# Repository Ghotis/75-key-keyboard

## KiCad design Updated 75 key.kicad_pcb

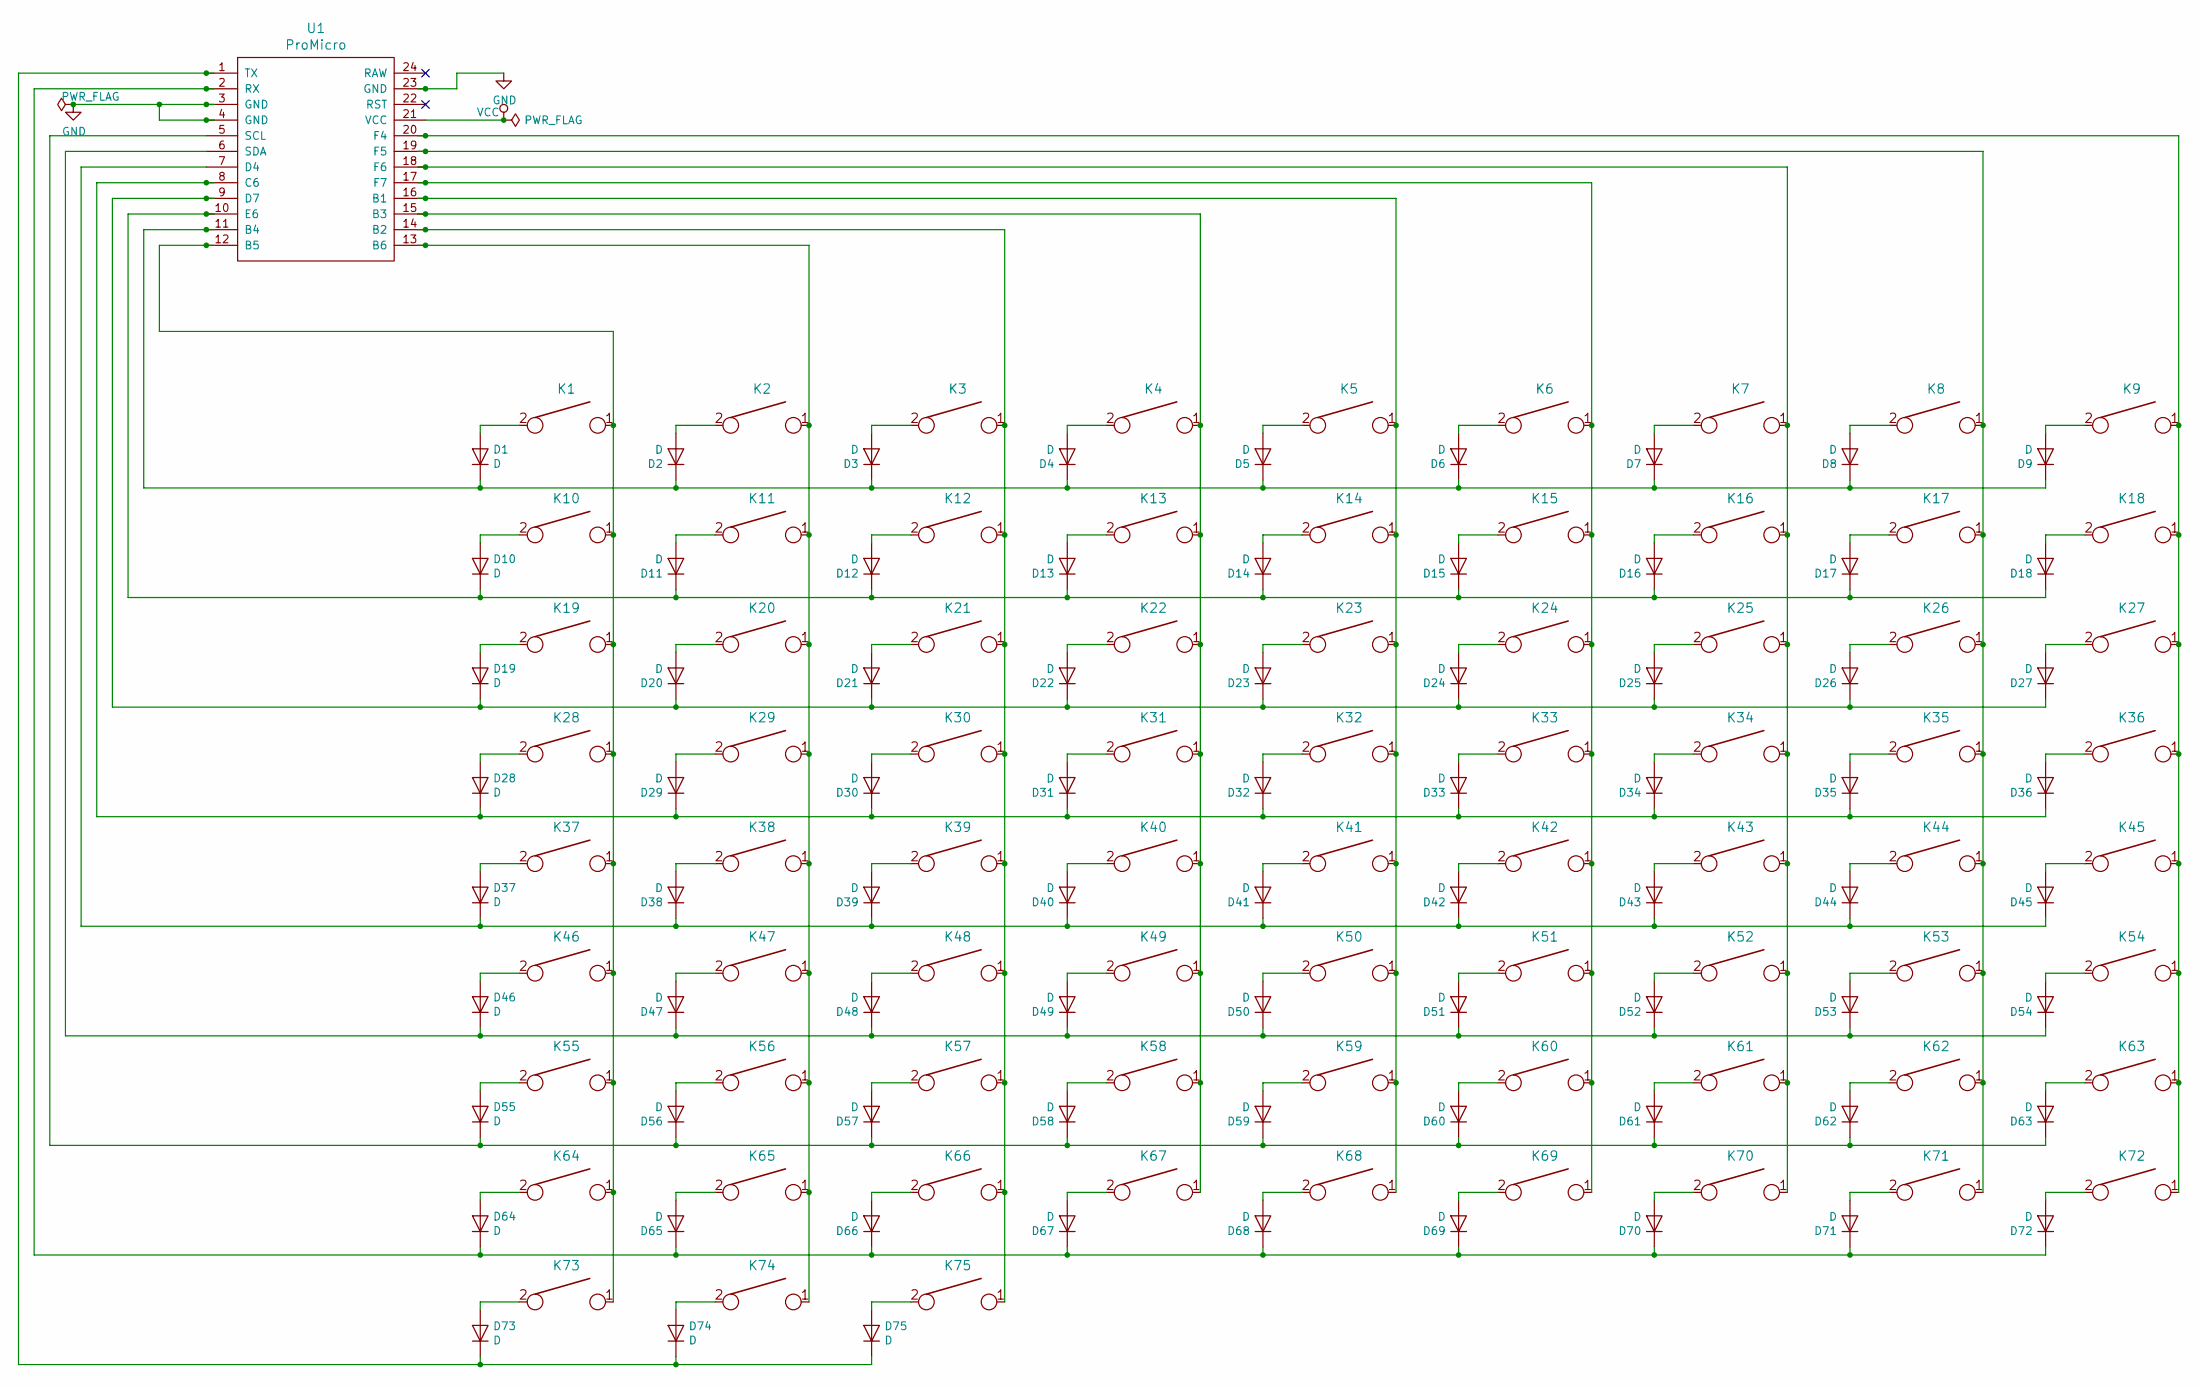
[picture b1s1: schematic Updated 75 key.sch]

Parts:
D1, D2, D3, D4, D5, D6, D7, D8, D9, D10, D11, D12, D13, D14, D15, D16, D17, D18, D19, D20, D21, D22, D23, D24, D25, D26, D27, D28, D29, D30, D31, D32, D33, D34, D35, D36, D37, D38, D39, D40, D41, D42, D43, D44, D45, D46, D47, D48, D49, D50, D51, D52, D53, D54, D55, D56, D57, D58, D59, D60, D61, D62, D63, D64, D65, D66, D67, D68, D69, D70, D71, D72, D73, D74, D75: D; D_SOD123_axial
K1, K2, K3, K4, K5, K6, K7, K8, K9, K10, K11, K12, K13, K14, K15, K16, K17, K18, K19, K20, K21, K22, K23, K24, K25, K26, K27, K28, K29, K30, K31, K32, K33, K34, K35, K36, K37, K38, K39, K40, K41, K42, K43, K44, K45, K46, K47, K48, K49, K50, K51, K52, K53, K54, K55, K56, K57, K58, K59, K60, K61, K62, K63, K64, K65, K66, K67, K68, K69, K70, K71, K72, K73, K74, K75: KEYSW; SW_Cherry_MX1A_1.00u_Plate
U1: ProMicro

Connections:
GND: U1.3 (GND), U1.4 (GND), U1.23 (GND)
unnamed: D1.1 (K), D2.1 (K), D3.1 (K), D4.1 (K), D5.1 (K), D6.1 (K), D7.1 (K), D8.1 (K), D9.1 (K), U1.11 (B4)
unnamed: D1.2 (A), K1.2
unnamed: D2.2 (A), K2.2
unnamed: D3.2 (A), K3.2
unnamed: D4.2 (A), K4.2
unnamed: D5.2 (A), K5.2
unnamed: D6.2 (A), K6.2
unnamed: D7.2 (A), K7.2
unnamed: D8.2 (A), K8.2
unnamed: D9.2 (A), K9.2
unnamed: D10.1 (K), D11.1 (K), D12.1 (K), D13.1 (K), D14.1 (K), D15.1 (K), D16.1 (K), D17.1 (K), D18.1 (K), U1.10 (E6)
unnamed: D10.2 (A), K10.2
unnamed: D11.2 (A), K11.2
unnamed: D12.2 (A), K12.2
unnamed: D13.2 (A), K13.2
unnamed: D14.2 (A), K14.2
unnamed: D15.2 (A), K15.2
unnamed: D16.2 (A), K16.2
unnamed: D17.2 (A), K17.2
unnamed: D18.2 (A), K18.2
unnamed: D19.1 (K), D20.1 (K), D21.1 (K), D22.1 (K), D23.1 (K), D24.1 (K), D25.1 (K), D26.1 (K), D27.1 (K), U1.9 (D7)
unnamed: D19.2 (A), K19.2
unnamed: D20.2 (A), K20.2
unnamed: D21.2 (A), K21.2
unnamed: D22.2 (A), K22.2
unnamed: D23.2 (A), K23.2
unnamed: D24.2 (A), K24.2
unnamed: D25.2 (A), K25.2
unnamed: D26.2 (A), K26.2
unnamed: D27.2 (A), K27.2
unnamed: D28.1 (K), D29.1 (K), D30.1 (K), D31.1 (K), D32.1 (K), D33.1 (K), D34.1 (K), D35.1 (K), D36.1 (K), U1.8 (C6)
unnamed: D28.2 (A), K28.2
unnamed: D29.2 (A), K29.2
unnamed: D30.2 (A), K30.2
unnamed: D31.2 (A), K31.2
unnamed: D32.2 (A), K32.2
unnamed: D33.2 (A), K33.2
unnamed: D34.2 (A), K34.2
unnamed: D35.2 (A), K35.2
unnamed: D36.2 (A), K36.2
unnamed: D37.1 (K), D38.1 (K), D39.1 (K), D40.1 (K), D41.1 (K), D42.1 (K), D43.1 (K), D44.1 (K), D45.1 (K), U1.7 (D4)
unnamed: D37.2 (A), K37.2
unnamed: D38.2 (A), K38.2
unnamed: D39.2 (A), K39.2
unnamed: D40.2 (A), K40.2
unnamed: D41.2 (A), K41.2
unnamed: D42.2 (A), K42.2
unnamed: D43.2 (A), K43.2
unnamed: D44.2 (A), K44.2
unnamed: D45.2 (A), K45.2
unnamed: D46.1 (K), D47.1 (K), D48.1 (K), D49.1 (K), D50.1 (K), D51.1 (K), D52.1 (K), D53.1 (K), D54.1 (K), U1.6 (SDA)
unnamed: D46.2 (A), K46.2
unnamed: D47.2 (A), K47.2
unnamed: D48.2 (A), K48.2
unnamed: D49.2 (A), K49.2
unnamed: D50.2 (A), K50.2
unnamed: D51.2 (A), K51.2
unnamed: D52.2 (A), K52.2
unnamed: D53.2 (A), K53.2
unnamed: D54.2 (A), K54.2
unnamed: D55.1 (K), D56.1 (K), D57.1 (K), D58.1 (K), D59.1 (K), D60.1 (K), D61.1 (K), D62.1 (K), D63.1 (K), U1.5 (SCL)
unnamed: D55.2 (A), K55.2
unnamed: D56.2 (A), K56.2
unnamed: D57.2 (A), K57.2
unnamed: D58.2 (A), K58.2
unnamed: D59.2 (A), K59.2
unnamed: D60.2 (A), K60.2
unnamed: D61.2 (A), K61.2
unnamed: D62.2 (A), K62.2
unnamed: D63.2 (A), K63.2
unnamed: D64.1 (K), D65.1 (K), D66.1 (K), D67.1 (K), D68.1 (K), D69.1 (K), D70.1 (K), D71.1 (K), D72.1 (K), U1.2 (RX)
unnamed: D64.2 (A), K64.2
unnamed: D65.2 (A), K65.2
unnamed: D66.2 (A), K66.2
unnamed: D67.2 (A), K67.2
unnamed: D68.2 (A), K68.2
unnamed: D69.2 (A), K69.2
unnamed: D70.2 (A), K70.2
unnamed: D71.2 (A), K71.2
unnamed: D72.2 (A), K72.2
unnamed: D73.1 (K), D74.1 (K), D75.1 (K), U1.1 (TX)
unnamed: D73.2 (A), K73.2
unnamed: D74.2 (A), K74.2
unnamed: D75.2 (A), K75.2
unnamed: K1.1, K10.1, K19.1, K28.1, K37.1, K46.1, K55.1, K64.1, K73.1, U1.12 (B5)
unnamed: K2.1, K11.1, K20.1, K29.1, K38.1, K47.1, K56.1, K65.1, K74.1, U1.13 (B6)
unnamed: K3.1, K12.1, K21.1, K30.1, K39.1, K48.1, K57.1, K66.1, K75.1, U1.14 (B2)
unnamed: K4.1, K13.1, K22.1, K31.1, K40.1, K49.1, K58.1, K67.1, U1.15 (B3)
unnamed: K5.1, K14.1, K23.1, K32.1, K41.1, K50.1, K59.1, K68.1, U1.16 (B1)
unnamed: K6.1, K15.1, K24.1, K33.1, K42.1, K51.1, K60.1, K69.1, U1.17 (F7)
unnamed: K7.1, K16.1, K25.1, K34.1, K43.1, K52.1, K61.1, K70.1, U1.18 (F6)
unnamed: K8.1, K17.1, K26.1, K35.1, K44.1, K53.1, K62.1, K71.1, U1.19 (F5)
unnamed: K9.1, K18.1, K27.1, K36.1, K45.1, K54.1, K63.1, K72.1, U1.20 (F4)
VCC: U1.21 (VCC)

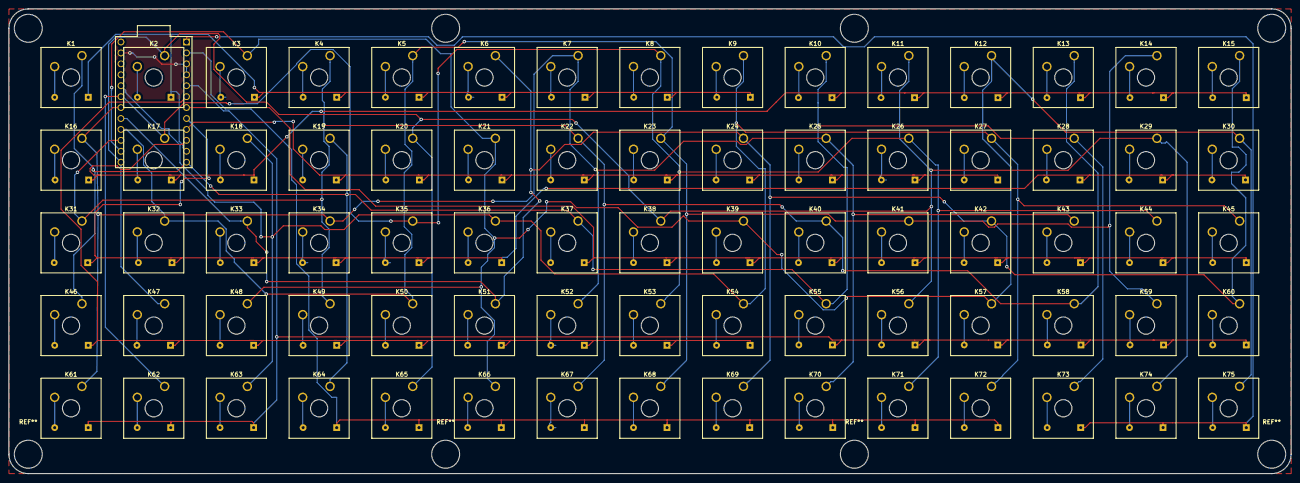
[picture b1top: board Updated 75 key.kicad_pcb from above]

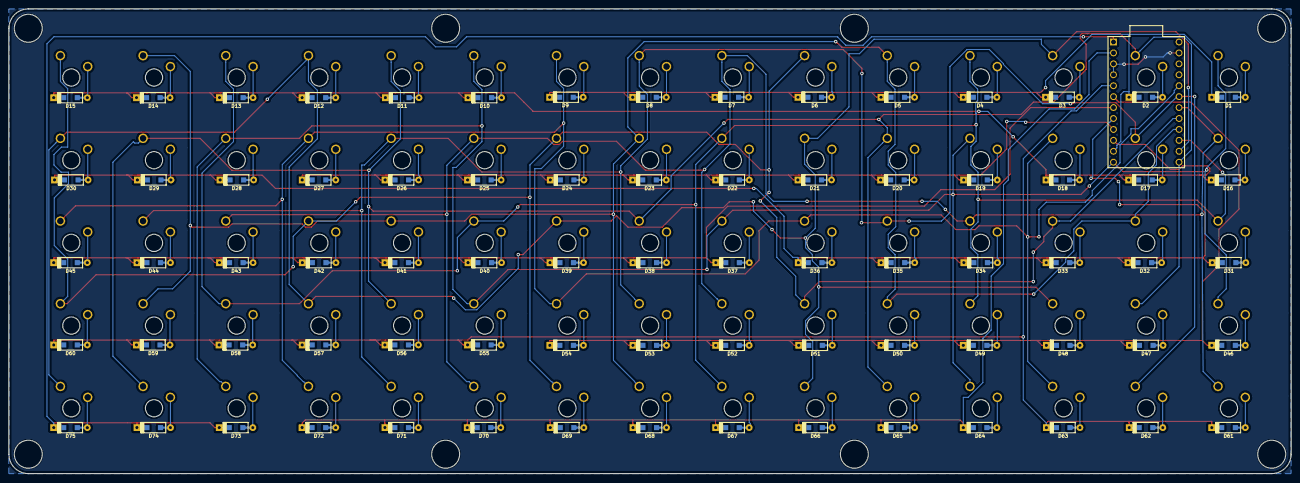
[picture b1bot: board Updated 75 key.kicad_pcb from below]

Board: 2 copper layers, 298.0 x 108.0 mm, 151 parts (76 on the bottom side), 94 nets.
